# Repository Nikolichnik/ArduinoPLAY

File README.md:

# ArduinoPLAY
<h4>SMD based breakout board for Arduino Nano development kit.</h4>

On pins 3, 5 and 6 there are tracks for connection suitable for small SMD NPN transistors (such as MMBT2222A) for driving LEDs or some other light load.

<br>

<p align="center">
  
</p>

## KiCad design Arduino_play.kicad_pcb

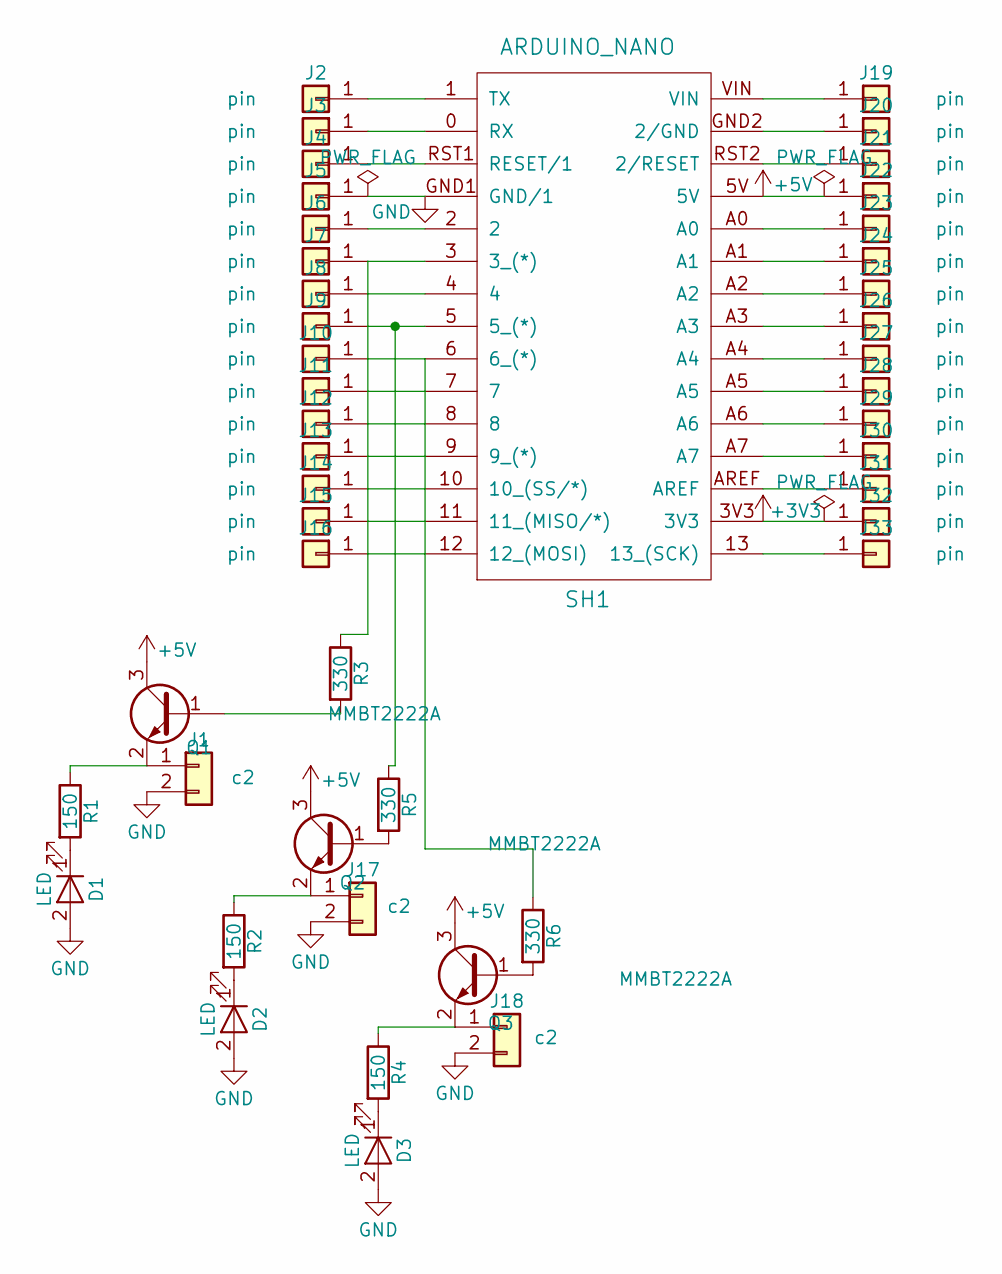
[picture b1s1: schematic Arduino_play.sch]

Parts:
D1, D2, D3: LED; LED_D3.0mm
J1, J17, J18: c2; Pin_Header_Angled_1x02_Pitch2.54mm
J2, J3, J4, J5, J6, J7, J8, J9, J10, J11, J12, J13, J14, J15, J16, J19, J20, J21, J22, J23, J24, J25, J26, J27, J28, J29, J30, J31, J32, J33: pin; Pin_Header_Angled_1x01_Pitch2.54mm
Q1, Q2, Q3: MMBT2222A; SOT-23
R1, R2, R4: 150; R_0805
R3, R5, R6: 330; R_0805
SH1: ARDUINO_NANO; ARDUINO_NANO_2_CONTOUR_ELL

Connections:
+3V3: J32.1, SH1.3V3
+5V: J22.1, Q1.3 (C), Q2.3 (C), Q3.3 (C), SH1.5V
GND: D1.2 (A), D2.2 (A), D3.2 (A), J1.2, J5.1, J17.2, J18.2, SH1.GND1 (GND/1)
unnamed: D1.1 (K), R1.2
unnamed: D2.1 (K), R2.2
unnamed: D3.1 (K), R4.2
unnamed: J1.1, Q1.2 (E), R1.1
unnamed: J2.1, SH1.1 (TX)
unnamed: J3.1, SH1.0 (RX)
unnamed: J4.1, SH1.RST1 (RESET/1)
unnamed: J6.1, SH1.2
unnamed: J7.1, R3.1, SH1.3 (3_(*))
unnamed: J8.1, SH1.4
unnamed: J9.1, R5.1, SH1.5 (5_(*))
unnamed: J10.1, R6.1, SH1.6 (6_(*))
unnamed: J11.1, SH1.7
unnamed: J12.1, SH1.8
unnamed: J13.1, SH1.9 (9_(*))
unnamed: J14.1, SH1.10 (10_(SS/*))
unnamed: J15.1, SH1.11 (11_(MISO/*))
unnamed: J16.1, SH1.12 (12_(MOSI))
unnamed: J17.1, Q2.2 (E), R2.1
unnamed: J18.1, Q3.2 (E), R4.1
unnamed: J19.1, SH1.VIN
unnamed: J20.1, SH1.GND2 (2/GND)
unnamed: J21.1, SH1.RST2 (2/RESET)
unnamed: J23.1, SH1.A0
unnamed: J24.1, SH1.A1
unnamed: J25.1, SH1.A2
unnamed: J26.1, SH1.A3
unnamed: J27.1, SH1.A4
unnamed: J28.1, SH1.A5
unnamed: J29.1, SH1.A6
unnamed: J30.1, SH1.A7
unnamed: J31.1, SH1.AREF
unnamed: J33.1, SH1.13 (13_(SCK))
unnamed: Q1.1 (B), R3.2
unnamed: Q2.1 (B), R5.2
unnamed: Q3.1 (B), R6.2

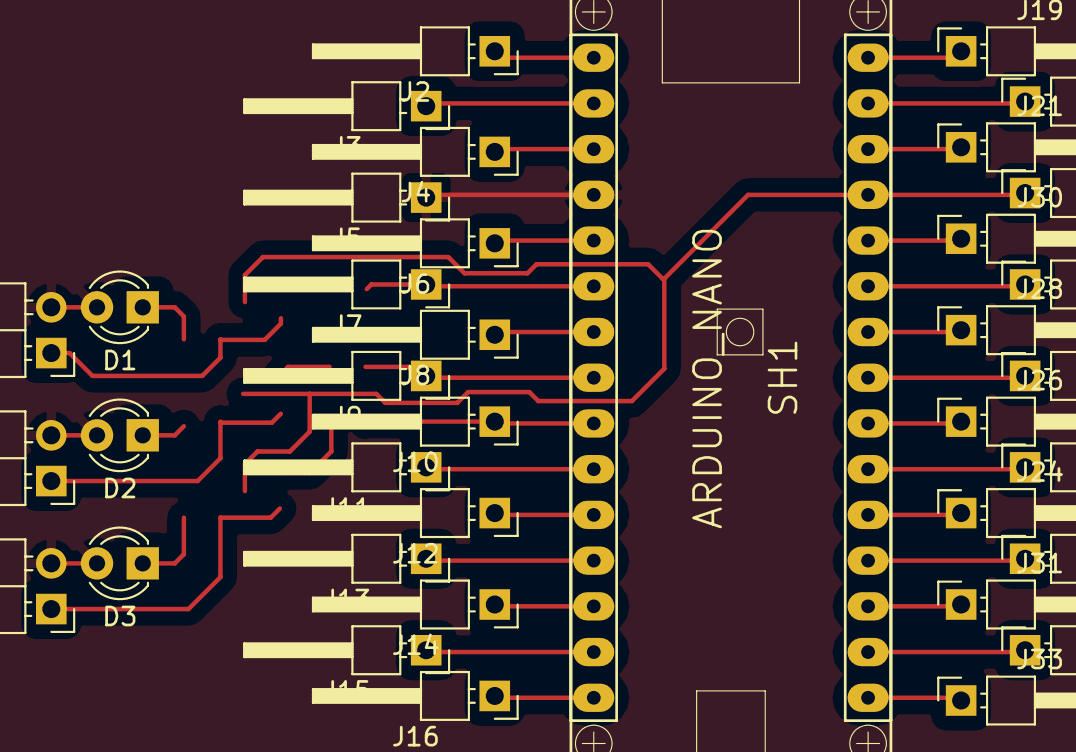
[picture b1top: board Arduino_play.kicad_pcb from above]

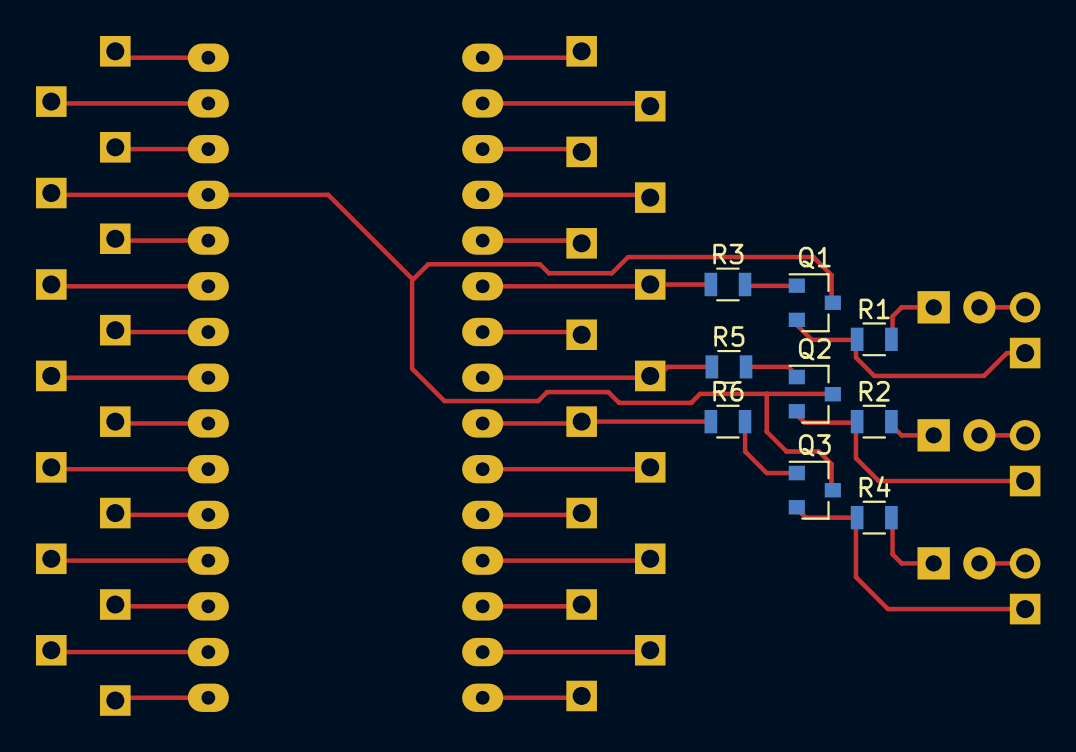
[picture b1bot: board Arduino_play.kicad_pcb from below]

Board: 2 copper layers, 46 parts (9 on the bottom side), 39 nets.
